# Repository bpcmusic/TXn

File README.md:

# TXn - Eurorack Fixed Panner/Mixer

The TELEXn (TXn) is a 2HP Remix of Jesper Särnesjö's open source module "nearness". Nearness is an ingenious module that you absolutely need in your rig. This remix compresses the original 3HP module into 2HP. You really can't go wrong with either one.

## What it Does

The module mixes and pans seven inputs to two outputs. There is an output at the top and bottom of the panel. Between these outputs are the seven inputs. These patch points correspond to panning positions between the two outputs. The closer you are to an output, the louder your signal will be there (and the quieter it will be in the corresponding output).

## How the TXn is Different from the 3HP Nearness

Again - all of the credit belongs with the original [Nearness Module](https://github.com/bpcmusic/nearness). The TXn is simply a reduced-form-factor version. A few changes needed to be made in order to accomplish this:

* The TXn is 1HP Smaller than Nearness (2HP vs 3HP).
* The TXn has a Power Section that is Different than the One on Nearness.
* The two boards on the TXn are oriented 90 degrees from each other (which can be tricky to solder).
* The TXn has a 1x5 power connector that hangs off the back of the module; its 6dB pad jumper connectors also hang off the back of the module.
* The TXn requires that the jacks be slightly raised off the top board in order to avoid electrical contact with the headers positioned underneath them. In fact, you will need to make sure you trim the headers flush with the top of the board priod to soldering. This is a real PITA, btw.

That's it.

If you are thinking you'd like to DIY a Nearness - it is highly recommended to consider building the 3HP version. It is much easier to solder and assemble.

## Module Specifications

* +12V: 25 mA  
* -12V: 26 mA  
* +5V: 0 mA  
* 2HP Width 
* 19mm Depth

## Folders & Files Explained

* **assistive**: 
	* ```TXn Build Guide.pdf``` - a PDF build guide to walk your through component-level placement
	* ```TXn Assembler.svg``` - little laser-cut forms to hold your boards together when soldering the 90 degree angle.
	* ```TXn Frame``` - a 3D printed frame to hold multiple TXn at a time
	* ```TXn Stencil Frame``` - a 3D printed stencil frame to hold the TXn in place while applying solder paste
	* ```TXn Stencil.svg``` - the solder paste stencil for laser cutting
	
* **board**
	* ```gerbers``` - the gerbers files (and Eagle files) for the top and bottom boards
	* ```images``` - image rederings of the boards
	* ```TXn_v1.2.brd/sch``` - the master Eagle file for the TXn
	
* **extras**
	* ```instructions.docx``` - the instructions delivered with the pre-built module
	* ```txn_mix_diagram.ai/svg``` - a digram of the module's mix behavior (used in the instructions file)
	
* **panel**
	* ```metalphoto``` - the individual files used for the creation of the metalphoto panel in the retail version
	* ```TXn.ai/svg``` - the panel files
	* ```TXn_lg.png``` - a big version of the panel
	* ```TXn_mp.zip``` - the archive sent for fabrication
	* ```TXn_sm.png``` - a small photo of the panel

* ```TXn BOM.csv``` - the BOM for this version of the TXb.

## Links

Nearness can be found in this repository:

* [Nearness Repository](https://github.com/bpcmusic/nearness)

Visit the TXn on Modular Grid:

* [Modular Grid](https://www.modulargrid.net/e/other-unknown-telexn)

Pre-built TXn are occasionally made availalbe for purchase here:

* [store.bpcmusic.com](https://store.bpcmusic.com/products/telexn?variant=5636075159583)

## License

[CC BY-SA 4.0](http://creativecommons.org/licenses/by-sa/4.0/)

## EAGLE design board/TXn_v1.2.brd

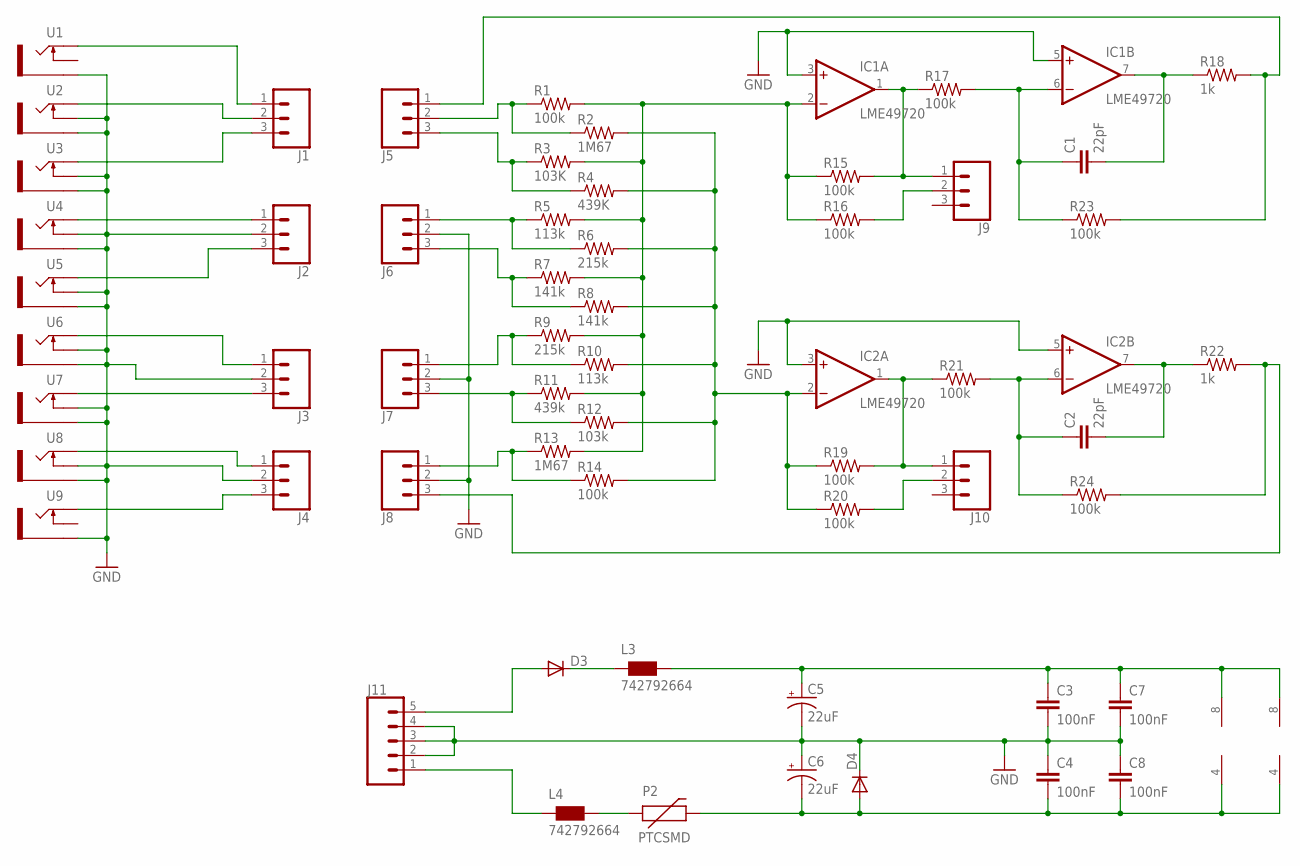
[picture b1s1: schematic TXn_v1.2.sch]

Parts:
C1, C2: 22pF; 0603-CAP
C3, C4, C7, C8: 100nF; 0603-CAP
C5, C6: 22uF; PANASONIC_B
D3, D4: DIODE-SOD123; SOD123
IC1, IC2: LME49720; SO08
J1, J2, J3, J4, J5, J6, J7, J8, J9, J10: CONN_031X03_NO_SILK; 1X03_NO_SILK
J11: CONN_05NO_SILK; 1X05_NO_SILK
L3, L4: 742792664; 0603
P2: PTCSMD; PTC-1206
R1, R14, R15, R16, R17, R19, R20, R21, R23, R24: 100k; R0603
R2, R13: 1M67; R0603
R3: 103K; R0603
R4: 439K; R0603
R5, R10: 113k; R0603
R6, R9: 215k; R0603
R7, R8: 141k; R0603
R11: 439k; R0603
R12: 103k; R0603
R18, R22: 1k; R0603
U1, U2, U3, U4, U5, U6, U7, U8, U9: THONKICONNLEFT; WQP-PJ301M-12_JACK_L

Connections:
BMIX: IC2.2 (-IN), R2.2, R4.2, R6.2, R8.2, R10.2, R12.2, R14.2, R19.1, R20.1
BOUT: J8.3, R22.2, R24.2
GND: C3.2, C4.1, C5.-, C6.+, C7.2, C8.1, D4.C, IC1.3 (+IN), IC1.5 (+IN), IC2.3 (+IN), IC2.5 (+IN), J2.2, J3.2, J4.2, J6.2, J7.2, J8.2, J11.2, J11.3, J11.4, U1.P$3_SLEEVE (SLEEVE), U2.P$2_SWITCH (SWITCH), U2.P$3_SLEEVE (SLEEVE), U3.P$2_SWITCH (SWITCH), U3.P$3_SLEEVE (SLEEVE), U4.P$2_SWITCH (SWITCH), U4.P$3_SLEEVE (SLEEVE), U5.P$2_SWITCH (SWITCH), U5.P$3_SLEEVE (SLEEVE), U6.P$2_SWITCH (SWITCH), U6.P$3_SLEEVE (SLEEVE), U7.P$2_SWITCH (SWITCH), U7.P$3_SLEEVE (SLEEVE), U8.P$2_SWITCH (SWITCH), U8.P$3_SLEEVE (SLEEVE), U9.P$3_SLEEVE (SLEEVE)
unnamed: J1.1, U1.P$1_TIP (TIP)
unnamed: J5.2, R1.1, R2.1
unnamed: J5.3, R3.1, R4.1
unnamed: J6.1, R5.1, R6.1
unnamed: J6.3, R7.1, R8.1
unnamed: J7.3, R11.1, R12.1
unnamed: J8.1, R13.1, R14.1
unnamed: J7.1, R9.1, R10.1
unnamed: J4.3, U9.P$1_TIP (TIP)
unnamed: J4.1, U8.P$1_TIP (TIP)
unnamed: J1.2, U2.P$1_TIP (TIP)
unnamed: J1.3, U3.P$1_TIP (TIP)
unnamed: J2.1, U4.P$1_TIP (TIP)
unnamed: J2.3, U5.P$1_TIP (TIP)
unnamed: J3.3, U7.P$1_TIP (TIP)
unnamed: IC2.1 (OUT), J10.1, R19.2, R21.1
unnamed: J3.1, U6.P$1_TIP (TIP)
unnamed: C2.1, IC2.6 (-IN), R21.2, R24.1
unnamed: IC1.1 (OUT), J9.1, R15.2, R17.1
unnamed: C1.1, IC1.6 (-IN), R17.2, R23.1
unnamed: C2.2, IC2.7 (OUT), R22.1
unnamed: J9.2, R16.2
unnamed: C1.2, IC1.7 (OUT), R18.1
unnamed: J10.2, R20.2
unnamed: D3.C, L3.1
unnamed: L4.2, P2.1
TMIX: IC1.2 (-IN), R1.2, R3.2, R5.2, R7.2, R9.2, R11.2, R13.2, R15.1, R16.1
TOUT: J5.1, R18.2, R23.2
VCC: C3.1, C5.+, C7.1, IC1.8 (V+), IC2.8 (V+), L3.2
VCC1: D3.A, J11.5
VEE: C4.2, C6.-, C8.2, D4.A, IC1.4 (V-), IC2.4 (V-), P2.2
VEE1: J11.1, L4.1

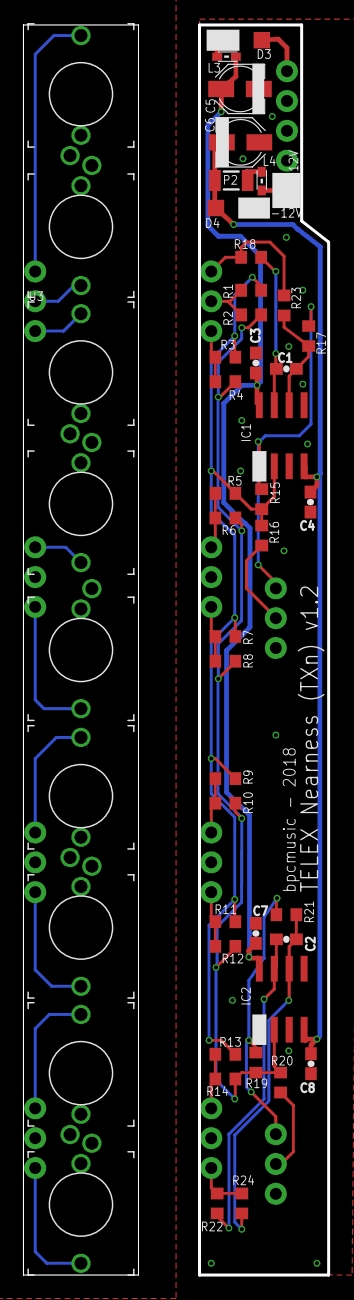
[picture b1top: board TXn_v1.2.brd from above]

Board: 2 copper layers, 25.9 x 106.5 mm, 59 parts (0 on the bottom side), 35 nets.

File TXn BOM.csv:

Qty,Value,Package,Parts,Description,Mouser Part Number,Alternate Mouser Part,Notes
6,1X03,1X03 Angled,"J1, J2, J3, J4, J5, J6, J7, J8, J9, J10",Header,538-22-28-8030,,
1,1X05,1X05 Angled,J11,Header,538-22-28-8050,,
2,Diode,SOD123,"D3, D4",Diode,621-1N5819HW-F,,
10,100k,R0603,"R1, R14, R15, R16, R17, R19, R20, R21, R23, R24",Resistor,667-ERA-3AEB104V,,
4,100nF,0603-CAP,"C3, C4, C7, C8",Capacitor,581-06035C104JAT2A,80-C0603X104J3R,
2,102k,R0603,"R3, R12",Resistor,667-ERA-3AEB1023V,,103k Calculated
2,113k,R0603,"R5, R10",Resistor,71-TNPW0603113KBEEA,,
2,140k,R0603,"R7, R8",Resistor,603-RT0603DRD07140KL,,141k Calculated
2,1M69,R0603,"R2, R13",Resistor,603-RC0603FR-071M69L,,1M67 Calculated; Thick Film :(
2,1k,R0603,"R18, R22",Resistor,66-WINT0603LF111001A,652-CRT0603BY1001EAS,
2,215k,R0603,"R6, R9",Resistor,667-ERA-3AEB2153V,,
2,22pF,0603-CAP,"C1, C2",Capacitor,80-C0603C220C5G,,
2,22uF,PANASONIC_B,"C5, C6",Polarized Capacitor,667-EEE-FT1E220AR,,
2,442k,R0603,"R4, R11",Resistor,603-RT0603DRE07442KL,,439k Calculated
2,742792664,603,"L3, L4",Ferrite Bead,710-742792664,,
2,LME49720,SO08,"IC1, IC2",OP AMP,926-LME49720MAX/NOPB,,
1,PTCSMD,PTC-1206,P2,Fuse PTC,576-1206L035/16YR,,
9,JACK,PJ301M,"U1, U2, U3, U4, U5, U6, U7, U8, U9",3.5mm Jack,,,

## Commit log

2019-02-12 added readme details
2019-02-12 added top board image
2019-02-14 slight copy change
2020-06-08 fixed mis-marked build guide

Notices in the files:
board/TXn_v1.2.brd:
based on nearness by Jesper Särnesjö - CC BY-SA 4.0
parts and their libraries:
SparkFun-Connectors: Licensing: Creative Commons ShareAlike 4.0 International - https://creativecommons.org/licenses/by-sa/4.0
